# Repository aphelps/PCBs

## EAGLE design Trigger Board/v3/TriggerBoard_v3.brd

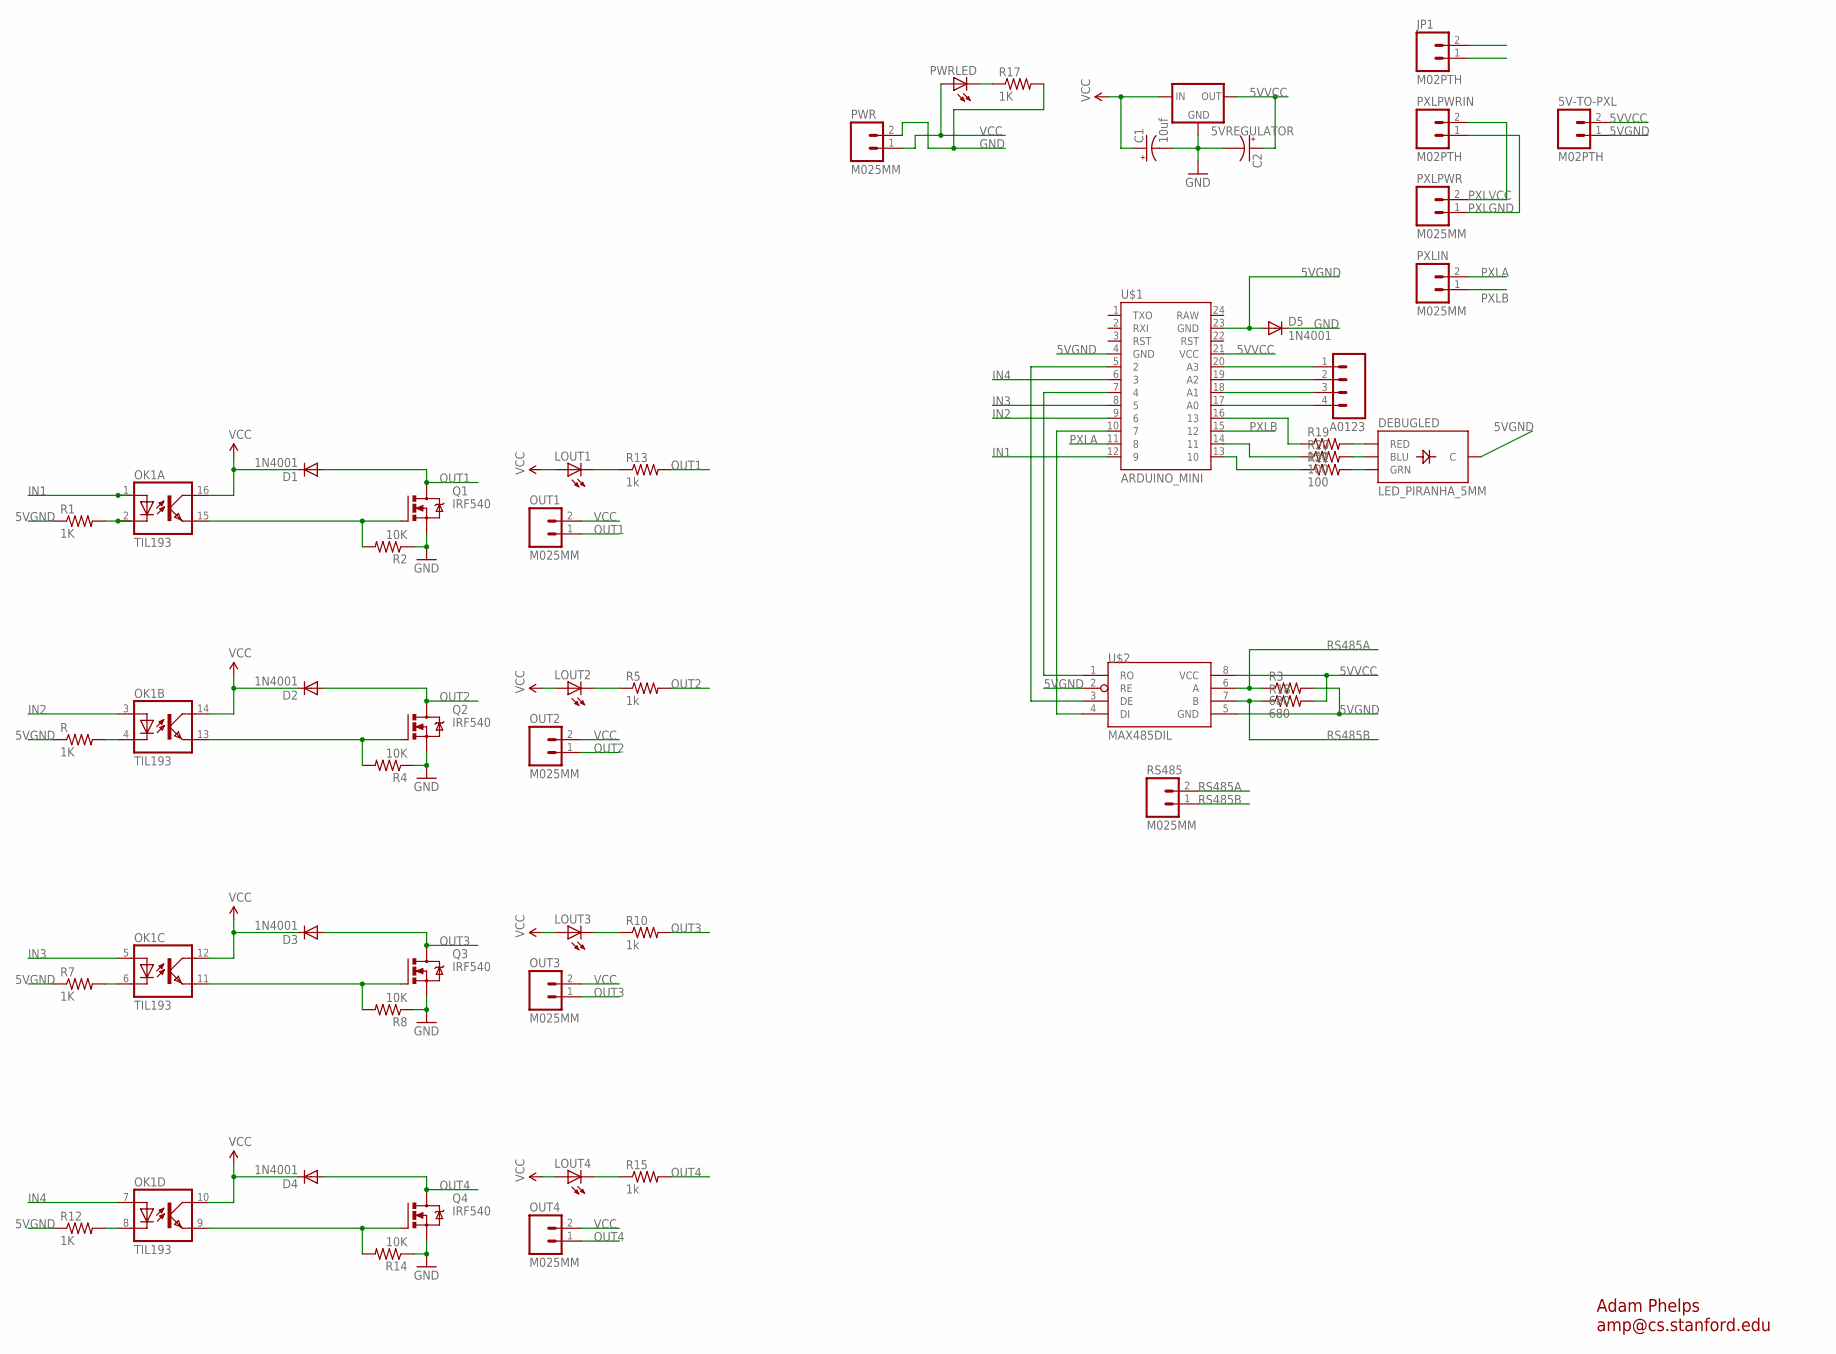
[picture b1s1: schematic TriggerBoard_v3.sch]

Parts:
5V-TO-PXL: M02PTH; 1X02
5VREGULATOR: V_REG_78XXSINK; TO220-IGO
A0123: M04PTH; 1X04
C1: 10uf; CPOL-RADIAL-10UF-25V
C2: CAP_POLPTH2; CPOL-RADIAL-10UF-25V
D1, D2, D3, D4: 1N4001; DIODE-1N4001
D5: 1N4001; DIODE-1N4001-KIT
DEBUGLED: LED_PIRANHA_5MM
JP1: M02PTH; 1X02
LOUT1, LOUT2, LOUT3, LOUT4: LED3MM
OK1: TIL193; DIL16
OUT1, OUT2, OUT3, OUT4: M025MM; SCREWTERMINAL-5MM-2
PWR: M025MM; SCREWTERMINAL-5MM-2
PWRLED: LED5MM
PXLIN: M025MM; SCREWTERMINAL-5MM-2
PXLPWR: M025MM; SCREWTERMINAL-5MM-2
PXLPWRIN: M02PTH; 1X02
Q1, Q2, Q3, Q4: IRF540; TO220BV
R, R1, R7, R12, R17: 1K; AXIAL-0.4
R2, R4, R8, R14: 10K; AXIAL-0.4
R3, R18: 680; AXIAL-0.4
R5, R10, R13, R15: 1k; AXIAL-0.4
R19: 150; AXIAL-0.4
R20, R21: 100; AXIAL-0.4
RS485: M025MM; SCREWTERMINAL-5MM-2
U$1: ARDUINO_MINI
U$2: MAX485DIL; DIL08

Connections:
5VGND: 5V-TO-PXL.1, D5.A, DEBUGLED.- (C), R.P$1 (1), R1.P$1 (1), R3.P$2 (2), R7.P$1 (1), R12.P$1 (1), U$1.4 (GND), U$1.23 (GND), U$2.2 (RE), U$2.5 (GND)
5VVCC: 5V-TO-PXL.2, 5VREGULATOR.OUT, C2.1 (+), R18.P$2 (2), U$1.21 (VCC), U$2.8 (VCC)
GND: 5VREGULATOR.GND, C1.2 (-), C2.2 (-), D5.C, JP1.1, PWR.2, Q1.S, Q2.S, Q3.S, Q4.S, R2.P$1 (1), R4.P$1 (1), R8.P$1 (1), R14.P$1 (1), R17.P$2 (2)
IN1: OK1.1 (A), U$1.12 (9)
IN2: OK1.3 (A), U$1.9 (6)
IN3: OK1.5 (A), U$1.8 (5)
IN4: OK1.7 (A), U$1.6 (3)
unnamed: LOUT1.K (C), R13.P$1 (1)
unnamed: OK1.4 (C), R.P$2 (2)
unnamed: A0123.4, U$1.17 (A0)
unnamed: OK1.15 (EMIT), Q1.G, R2.P$2 (2)
unnamed: OK1.13 (EMIT), Q2.G, R4.P$2 (2)
unnamed: OK1.2 (C), R1.P$2 (2)
unnamed: LOUT2.K (C), R5.P$1 (1)
unnamed: R21.P$1 (1), U$1.13 (10)
unnamed: OK1.11 (EMIT), Q3.G, R8.P$2 (2)
unnamed: LOUT3.K (C), R10.P$1 (1)
unnamed: OK1.6 (C), R7.P$2 (2)
unnamed: R20.P$1 (1), U$1.14 (11)
unnamed: OK1.9 (EMIT), Q4.G, R14.P$2 (2)
unnamed: LOUT4.K (C), R15.P$1 (1)
unnamed: OK1.8 (C), R12.P$2 (2)
unnamed: R19.P$1 (1), U$1.16 (13)
unnamed: PWRLED.K (C), R17.P$1 (1)
unnamed: A0123.3, U$1.18 (A1)
unnamed: U$1.5 (2), U$2.3 (DE)
unnamed: U$1.7 (4), U$2.1 (RO)
unnamed: U$1.10 (7), U$2.4 (DI)
unnamed: DEBUGLED.R (RED), R19.P$2 (2)
unnamed: DEBUGLED.B (BLU), R20.P$2 (2)
unnamed: DEBUGLED.G (GRN), R21.P$2 (2)
unnamed: A0123.2, U$1.19 (A2)
unnamed: A0123.1, U$1.20 (A3)
OUT1: D1.A, OUT1.1, Q1.D, R13.P$2 (2)
OUT2: D2.A, OUT2.1, Q2.D, R5.P$2 (2)
OUT3: D3.A, OUT3.1, Q3.D, R10.P$2 (2)
OUT4: D4.A, OUT4.1, Q4.D, R15.P$2 (2)
PXLA: PXLIN.2, U$1.11 (8)
PXLB: PXLIN.1, U$1.15 (12)
PXLGND: PXLPWR.1, PXLPWRIN.1
PXLVCC: PXLPWR.2, PXLPWRIN.2
RS485A: R3.P$1 (1), RS485.2, U$2.6 (A)
RS485B: R18.P$1 (1), RS485.1, U$2.7 (B)
VCC: 5VREGULATOR.IN, C1.1 (+), D1.C, D2.C, D3.C, D4.C, JP1.2, LOUT1.A, LOUT2.A, LOUT3.A, LOUT4.A, OK1.10 (COL), OK1.12 (COL), OK1.14 (COL), OK1.16 (COL), OUT1.2, OUT2.2, OUT3.2, OUT4.2, PWR.1, PWRLED.A

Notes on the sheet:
Adam Phelps amp@cs.stanford.edu

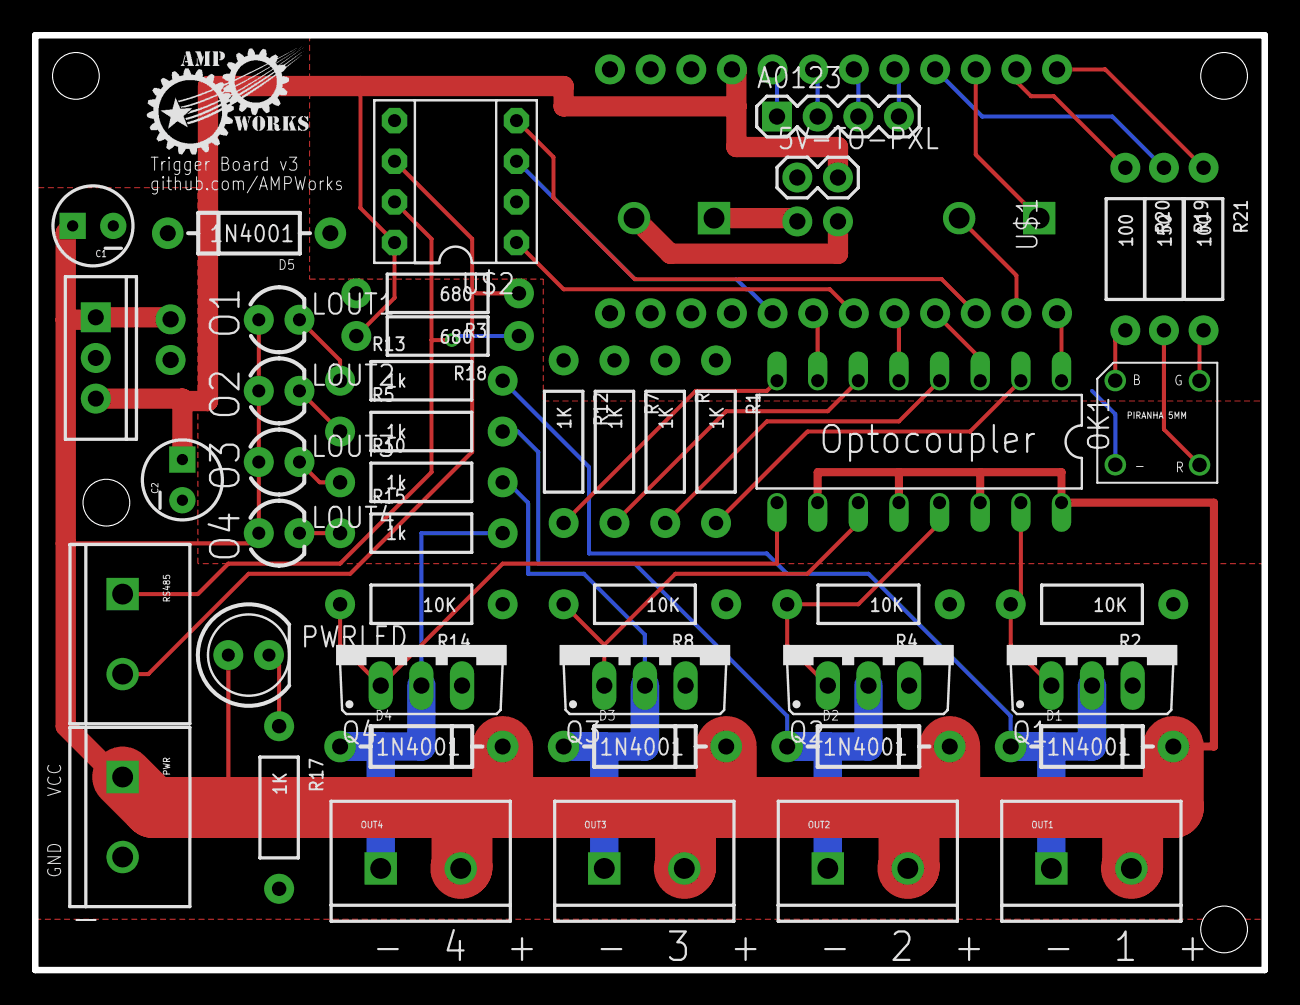
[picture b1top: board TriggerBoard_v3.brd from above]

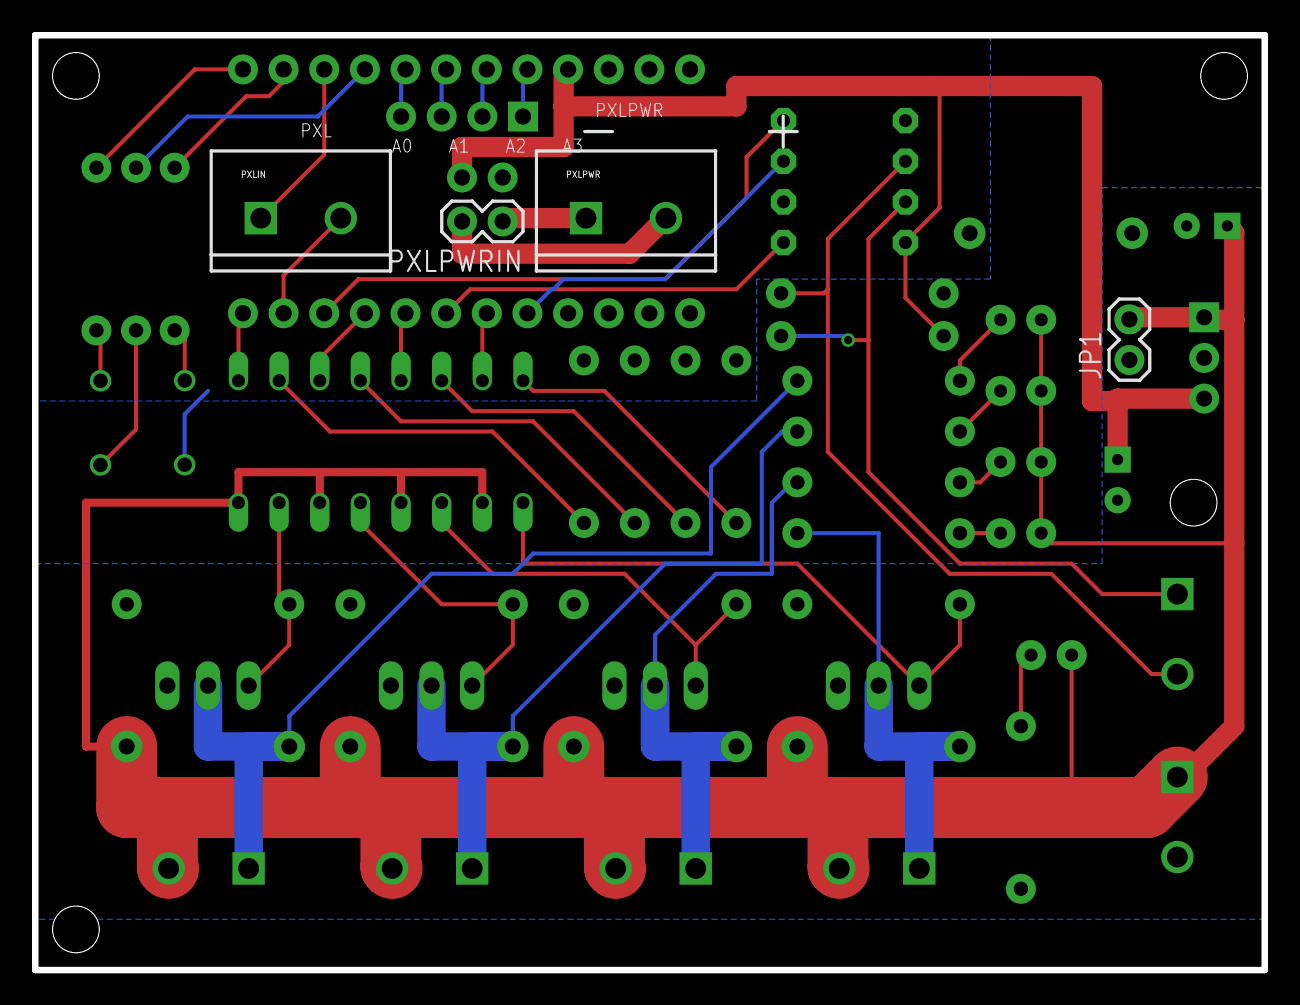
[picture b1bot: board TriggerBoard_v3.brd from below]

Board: 2 copper layers, 76.8 x 58.4 mm, 51 parts (4 on the bottom side), 44 nets.

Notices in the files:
parts and their libraries:
SparkFun-Connectors: Licensing: Creative Commons ShareAlike 4.0 International - https://creativecommons.org/licenses/by-sa/4.0
